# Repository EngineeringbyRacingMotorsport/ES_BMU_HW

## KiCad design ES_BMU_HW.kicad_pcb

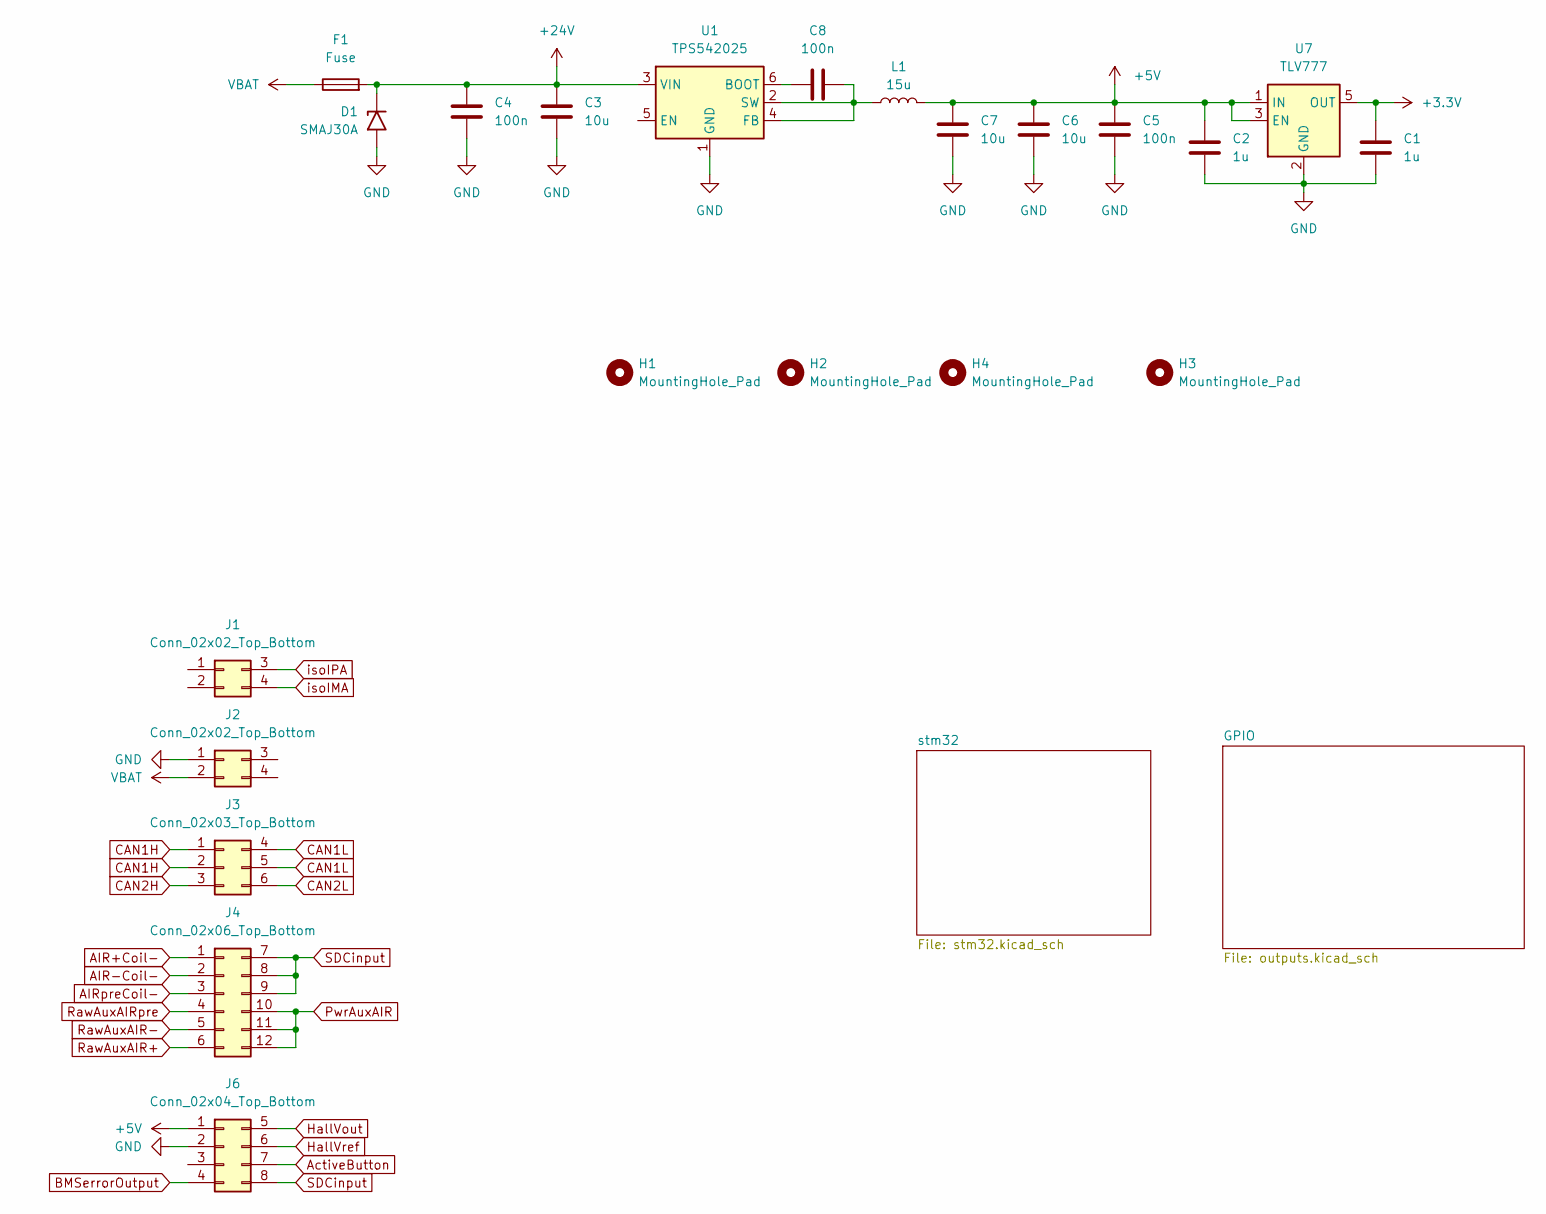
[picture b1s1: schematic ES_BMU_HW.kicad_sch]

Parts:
C1, C2: 1u; C_0603_1608Metric; Part Number VJ0603Y105KXXCW1BC
C3, C6, C7: 10u; C_1206_3216Metric; Part Number VJ1206G106KXATW1BC
C4, C5, C8: 100n; C_0603_1608Metric; Part Number VJ0603Y104KXACW1BC
D1: SMAJ30A; D_SMA; Part Number SMAJ30A
F1: Fuse; Fuse_1206_3216Metric; Part Number JB12S1001R
H1, H2, H3, H4: MountingHole_Pad; MountingHole_3.5mm
J1, J2: Conn_02x02_Top_Bottom; Molex_Nano-Fit_105314-xx04_2x02_P2.50mm_Horizontal
J3: Conn_02x03_Top_Bottom; Molex_Nano-Fit_105314-xx06_2x03_P2.50mm_Horizontal
J4: Conn_02x06_Top_Bottom; Molex_Nano-Fit_105314-xx12_2x06_P2.50mm_Horizontal
J6: Conn_02x04_Top_Bottom; Molex_Nano-Fit_105314-xx08_2x04_P2.50mm_Horizontal
L1: 15u; L_Vishay_IHLP-2020; Part Number IHLP2020CZER150M01
U1: TPS542025; SOT-23-6
U7: TLV777; SOT-23-5; Part Number TLV77712PDBVR

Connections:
+3.3V: C1.1, U7.5 (OUT); also elsewhere on the board
+5V: C2.1, C5.1, C6.1, C7.1, J6.1, L1.2, U7.1 (IN), U7.3 (EN); also elsewhere on the board
+24V: C3.1, C4.1, D1.1 (A1), F1.2, U1.3 (VIN); also elsewhere on the board
AIR+Coil-: J4.1; also elsewhere on the board
AIR-Coil-: J4.2; also elsewhere on the board
AIRpreCoil-: J4.3; also elsewhere on the board
ActiveButton: J6.7; also elsewhere on the board
BMSerrorOutput: J6.4; also elsewhere on the board
CAN1H: J3.1, J3.2; also elsewhere on the board
CAN1L: J3.4, J3.5; also elsewhere on the board
CAN2H: J3.3; also elsewhere on the board
CAN2L: J3.6; also elsewhere on the board
GND: C1.2, C2.2, C3.2, C4.2, C5.2, C6.2, C7.2, D1.2 (A2), J2.1, J6.2, U1.1 (GND), U7.2 (GND), U7.4 (GND); also elsewhere on the board
HallVout: J6.5; also elsewhere on the board
HallVref: J6.6; also elsewhere on the board
unnamed: C8.1, U1.6 (BOOT)
unnamed: C8.2, L1.1, U1.2 (SW), U1.4 (FB)
PwrAuxAIR: J4.10, J4.11, J4.12; also elsewhere on the board
RawAuxAIR+: J4.6; also elsewhere on the board
RawAuxAIR-: J4.5; also elsewhere on the board
RawAuxAIRpre: J4.4; also elsewhere on the board
SDCinput: J4.7, J4.8, J4.9, J6.8; also elsewhere on the board
VBAT: F1.1, J2.2; also elsewhere on the board
isoIMA: J1.4; also elsewhere on the board
isoIPA: J1.3; also elsewhere on the board

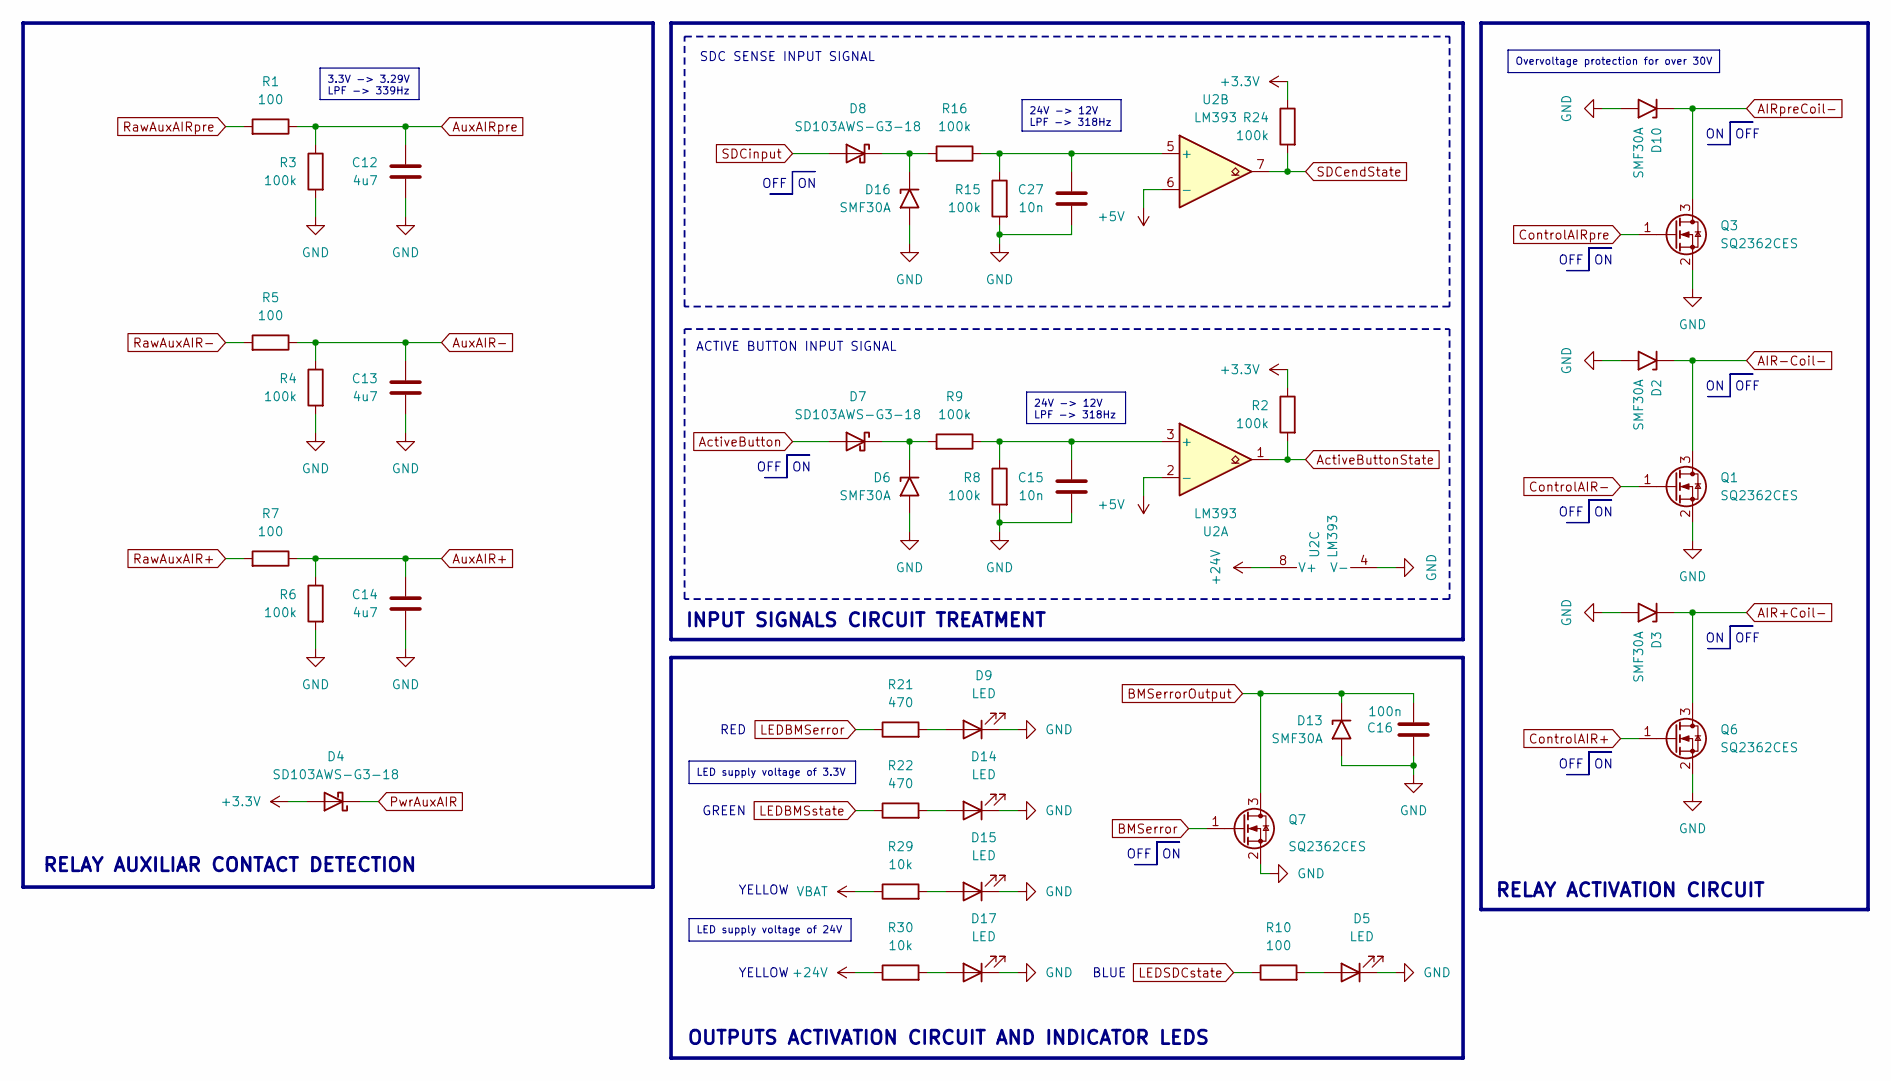
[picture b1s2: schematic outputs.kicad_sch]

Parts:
C12, C13, C14: 4u7; C_0603_1608Metric; Part Number VJ0603G475KXJCW1BC
C15, C27: 10n; C_0603_1608Metric; Part Number VJ0603Y103KXXCW1BC
C16: 100n; C_0603_1608Metric; Part Number VJ0603Y104KXACW1BC
D2, D3, D6, D10, D13, D16: SMF30A; D_SMF; Part Number SMF30A
D4, D7, D8: SD103AWS-G3-18; D_SOD-323_HandSoldering; Part Number SD103AWS-G3-18
D5: LED; LED_0603_1608Metric; Part Number VLMB1300-GS08
D9: LED; LED_0603_1608Metric; Part Number VLMS1300-GS08
D14: LED; LED_0603_1608Metric; Part Number VLMG1300-GS08
D15, D17: LED; LED_0603_1608Metric; Part Number VLMY1300-GS08
Q1, Q3, Q6, Q7: SQ2362CES; SOT-23; Part Number SQ2362CES-T1_GE3
R1, R5, R7: 100; R_0603_1608Metric; Part Number TNPW0603100RBEEA
R2, R3, R4, R6, R8, R9, R15, R16, R24: 100k; R_0603_1608Metric; Part Number TNPW0603100KBEEA
R10: 100; R_0603_1608Metric; Part Number TNPW0603470RBEEA
R21, R22: 470; R_0603_1608Metric; Part Number TNPW0603470RBEEA
R29, R30: 10k; R_0603_1608Metric; Part Number CRCW060310K0FKTAHP
U2: LM393; TSSOP-8_4.4x3mm_P0.65mm; Part Number LM393APWR

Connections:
+3.3V: D4.2 (A), R2.1, R24.1; also elsewhere on the board
+5V: U2.2 (-), U2.6 (-); also elsewhere on the board
+24V: R30.1, U2.8 (V+); also elsewhere on the board
AIR+Coil-: D3.1 (A1), Q6.3 (D); also elsewhere on the board
AIR-Coil-: D2.1 (A1), Q1.3 (D); also elsewhere on the board
AIRpreCoil-: D10.1 (A1), Q3.3 (D); also elsewhere on the board
ActiveButton: D7.2 (A); also elsewhere on the board
ActiveButtonState: R2.2, U2.1; also elsewhere on the board
AuxAIR+: C14.1, R6.1, R7.1; also elsewhere on the board
AuxAIR-: C13.1, R4.1, R5.1; also elsewhere on the board
AuxAIRpre: C12.1, R1.1, R3.1; also elsewhere on the board
BMSerror: Q7.1 (G); also elsewhere on the board
BMSerrorOutput: C16.2, D13.1 (A1), Q7.3 (D); also elsewhere on the board
ControlAIR+: Q6.1 (G); also elsewhere on the board
ControlAIR-: Q1.1 (G); also elsewhere on the board
ControlAIRpre: Q3.1 (G); also elsewhere on the board
GND: C12.2, C13.2, C14.2, C15.2, C16.1, C27.2, D2.2 (A2), D3.2 (A2), D5.1 (K), D6.2 (A2), D9.1 (K), D10.2 (A2), D13.2 (A2), D14.1 (K), D15.1 (K), D16.2 (A2), D17.1 (K), Q1.2 (S), Q3.2 (S), Q6.2 (S), Q7.2 (S), R3.2, R4.2, R6.2, R8.2, R15.2, U2.4 (V-); also elsewhere on the board
LEDBMSerror: R21.1; also elsewhere on the board
LEDBMSstate: R22.1; also elsewhere on the board
LEDSDCstate: R10.1; also elsewhere on the board
unnamed: D5.2 (A), R10.2
unnamed: D6.1 (A1), D7.1 (K), R9.2
unnamed: D9.2 (A), R21.2
unnamed: D14.2 (A), R22.2
unnamed: D15.2 (A), R29.2
unnamed: D8.1 (K), D16.1 (A1), R16.2
unnamed: D17.2 (A), R30.2
unnamed: C15.1, R8.1, R9.1, U2.3 (+)
unnamed: C27.1, R15.1, R16.1, U2.5 (+)
PwrAuxAIR: D4.1 (K); also elsewhere on the board
RawAuxAIR+: R7.2; also elsewhere on the board
RawAuxAIR-: R5.2; also elsewhere on the board
RawAuxAIRpre: R1.2; also elsewhere on the board
SDCendState: R24.2, U2.7; also elsewhere on the board
SDCinput: D8.2 (A); also elsewhere on the board
VBAT: R29.1; also elsewhere on the board

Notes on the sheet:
OFF
ACTIVE BUTTON INPUT SIGNAL
OFF
RED
BLUE
YELLOW
RELAY AUXILIAR CONTACT DETECTION
INPUT SIGNALS CIRCUIT TREATMENT
RELAY ACTIVATION CIRCUIT
SDC SENSE INPUT SIGNAL
OUTPUTS ACTIVATION CIRCUIT AND INDICATOR LEDS
GREEN
24V -> 12V LPF -> 318Hz
3.3V -> 3.29V LPF -> 339Hz
LED supply voltage of 3.3V
LED supply voltage of 24V
Overvoltage protection for over 30V

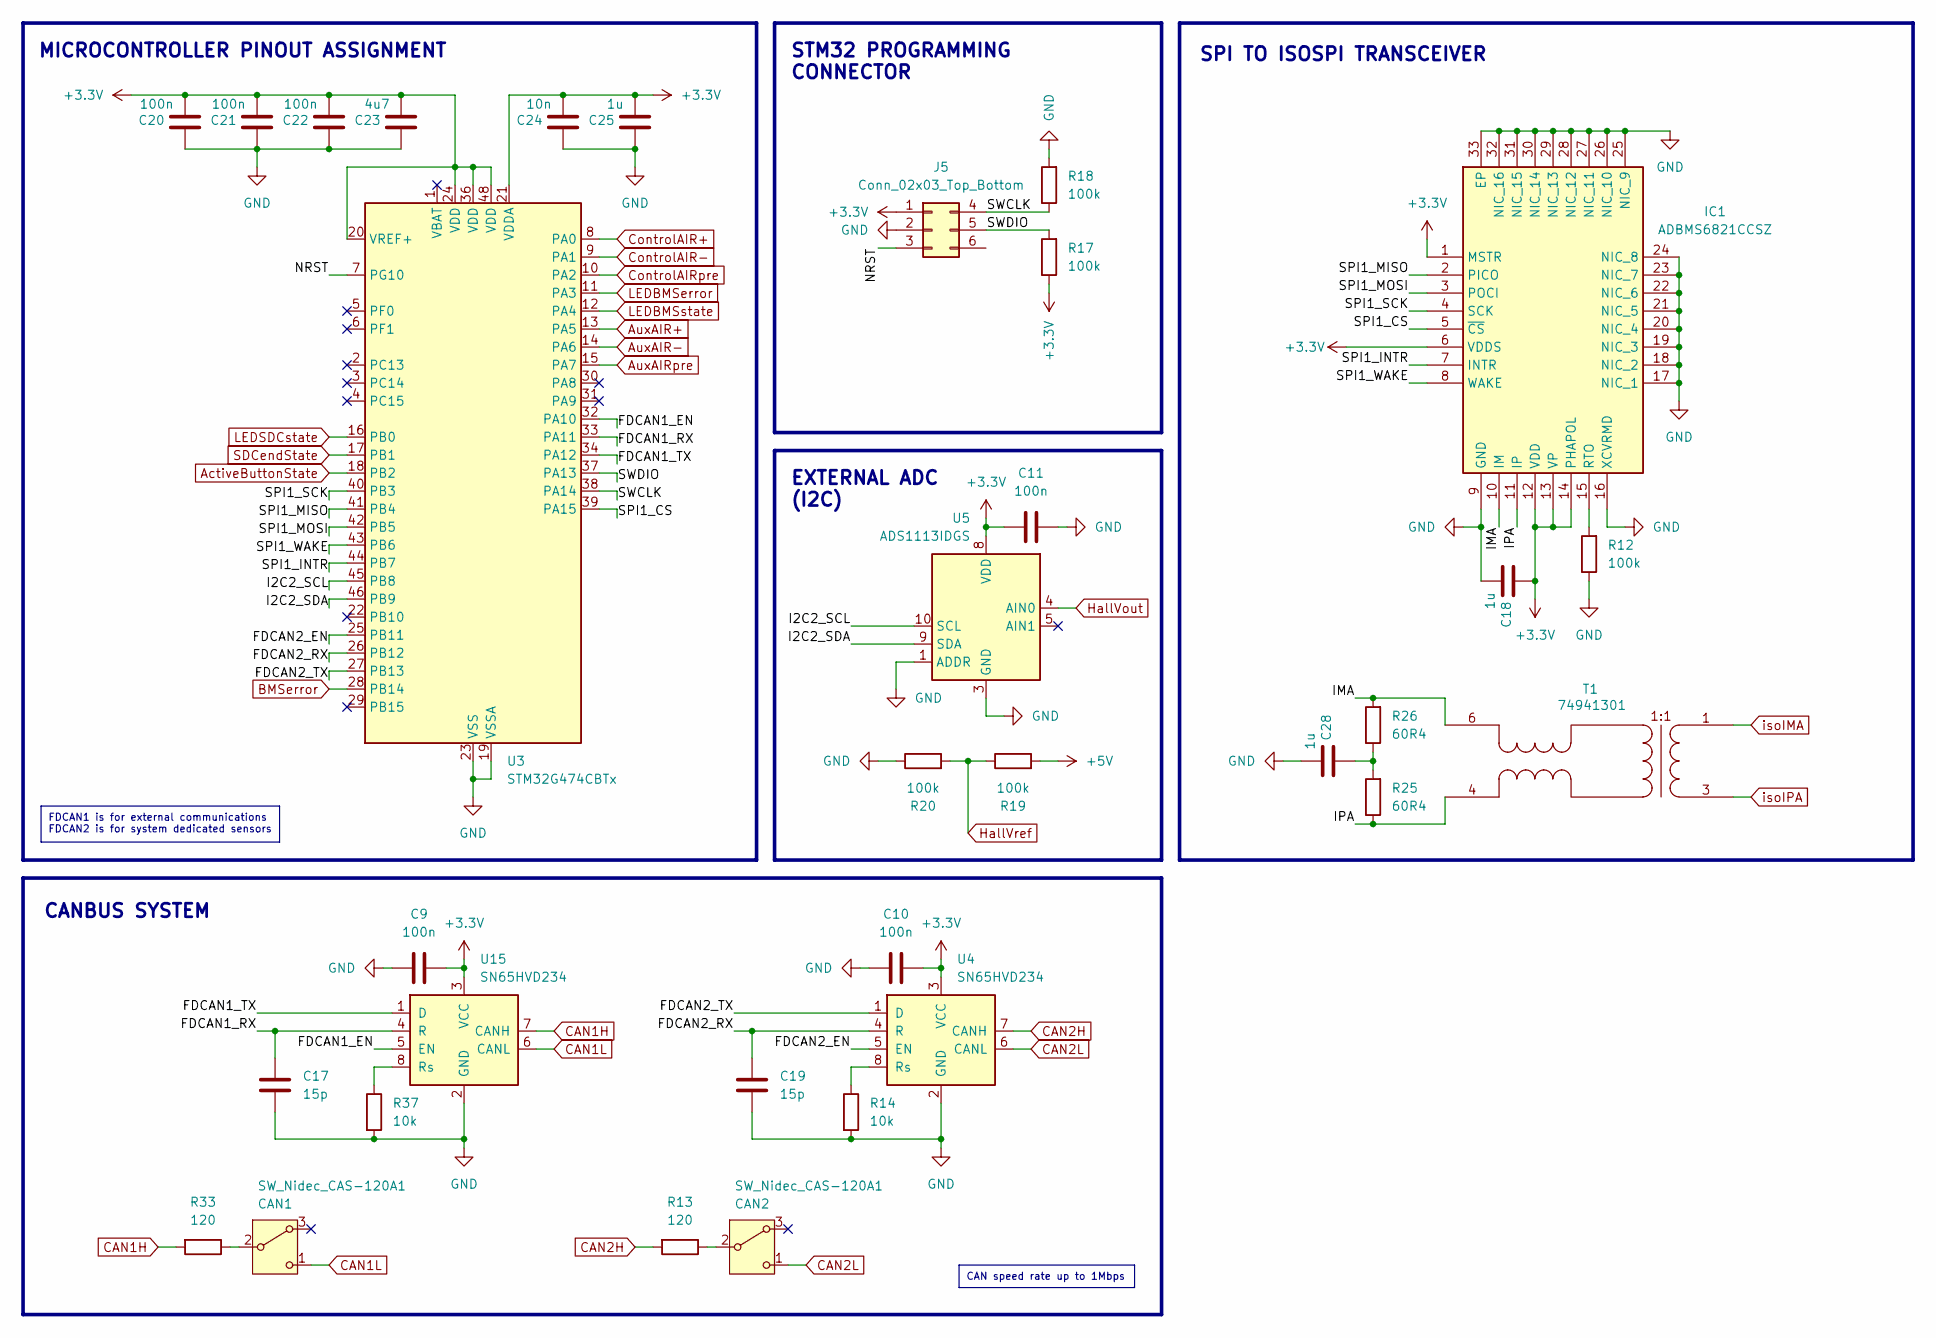
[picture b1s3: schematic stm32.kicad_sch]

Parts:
C9, C10, C11, C20, C21, C22: 100n; C_0603_1608Metric; Part Number VJ0603Y104KXACW1BC
C17, C19: 15p; C_0603_1608Metric; Part Number VJ0603A150JXXCW1BC
C18, C25, C28: 1u; C_0603_1608Metric; Part Number VJ0603Y105KXXCW1BC
C23: 4u7; C_0603_1608Metric; Part Number VJ0603G475KXJCW1BC
C24: 10n; C_0603_1608Metric; Part Number VJ0603Y103KXXCW1BC
CAN1, CAN2: SW_Nidec_CAS-120A1; Nidec_Copal_CAS-120A
IC1: ADBMS6821CCSZ; LFCSP-32-1EP_5x5mm_P0.5mm_EP3.1x3.1mm; Manufacturer_Part_Number ADBMS6821CCSZ; Mouser Part Number 584-ADBMS6821CCSZ
J5: Conn_02x03_Top_Bottom; PinHeader_2x03_P1.27mm_Vertical_SMD; Part Number 61000621121
R12, R17, R18, R19, R20: 100k; R_0603_1608Metric; Part Number TNPW0603100KBEEA
R13, R33: 120; R_0603_1608Metric; Part Number TNPW0603120RBEEA
R14, R37: 10k; R_0603_1608Metric; Part Number CRCW060310K0FKTAHP
R25, R26: 60R4; R_0603_1608Metric; Part Number TNPW060360R4BEEA
T1: 74941301; T_Wurth_WE-BMS_74941301; Working Voltage (V (DC)) 1000; Part Number 74941301
U3: STM32G474CBTx; LQFP-48_7x7mm_P0.5mm; Part Number STM32G474CBT3
U4, U15: SN65HVD234; SOIC-8_3.9x4.9mm_P1.27mm; Part Number SN65HVD234D
U5: ADS1113IDGS; TSSOP-10_3x3mm_P0.5mm; Part Number ADS1113IDGS

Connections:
+3.3V: C9.1, C10.1, C11.1, C18.1, C20.2, C21.2, C22.2, C23.2, C24.2, C25.2, IC1.1 (MSTR), IC1.6 (VDDS), IC1.12 (VDD), IC1.13 (VP), IC1.14 (PHAPOL), J5.1, R17.1, U3.20 (VREF+), U3.21 (VDDA), U3.24 (VDD), U3.36 (VDD), U3.48 (VDD), U4.3 (VCC), U5.8 (VDD), U15.3 (VCC); also elsewhere on the board
+5V: R19.2; also elsewhere on the board
/stm32/FDCAN1_EN: U3.32 (PA10), U15.5 (EN)
/stm32/FDCAN1_RX: C17.1, U3.33 (PA11), U15.4 (R)
/stm32/FDCAN1_TX: U3.34 (PA12), U15.1 (D)
/stm32/FDCAN2_EN: U3.25 (PB11), U4.5 (EN)
/stm32/FDCAN2_RX: C19.1, U3.26 (PB12), U4.4 (R)
/stm32/FDCAN2_TX: U3.27 (PB13), U4.1 (D)
/stm32/I2C2_SCL: U3.45 (PB8), U5.10 (SCL)
/stm32/I2C2_SDA: U3.46 (PB9), U5.9 (SDA)
/stm32/IMA: IC1.10 (IM), R26.2, T1.6
/stm32/IPA: IC1.11 (IP), R25.1, T1.4
/stm32/NRST: J5.3, U3.7 (PG10)
/stm32/SPI1_CS: IC1.5 (~CS), U3.39 (PA15)
/stm32/SPI1_INTR: IC1.7 (INTR), U3.44 (PB7)
/stm32/SPI1_MISO: IC1.2 (PICO), U3.41 (PB4)
/stm32/SPI1_MOSI: IC1.3 (POCI), U3.42 (PB5)
/stm32/SPI1_SCK: IC1.4 (SCK), U3.40 (PB3)
/stm32/SPI1_WAKE: IC1.8 (WAKE), U3.43 (PB6)
/stm32/SWCLK: J5.4, R18.1, U3.38 (PA14)
/stm32/SWDIO: J5.5, R17.2, U3.37 (PA13)
ActiveButtonState: U3.18 (PB2); also elsewhere on the board
AuxAIR+: U3.13 (PA5); also elsewhere on the board
AuxAIR-: U3.14 (PA6); also elsewhere on the board
AuxAIRpre: U3.15 (PA7); also elsewhere on the board
BMSerror: U3.28 (PB14); also elsewhere on the board
CAN1H: R33.2, U15.7 (CANH); also elsewhere on the board
CAN1L: CAN1.1 (C), U15.6 (CANL); also elsewhere on the board
CAN2H: R13.2, U4.7 (CANH); also elsewhere on the board
CAN2L: CAN2.1 (C), U4.6 (CANL); also elsewhere on the board
ControlAIR+: U3.8 (PA0); also elsewhere on the board
ControlAIR-: U3.9 (PA1); also elsewhere on the board
ControlAIRpre: U3.10 (PA2); also elsewhere on the board
GND: C9.2, C10.2, C11.2, C17.2, C18.2, C19.2, C20.1, C21.1, C22.1, C23.1, C24.1, C25.1, C28.2, IC1.9 (GND), IC1.16 (XCVRMD), IC1.17 (NIC_1), IC1.18 (NIC_2), IC1.19 (NIC_3), IC1.20 (NIC_4), IC1.21 (NIC_5), IC1.22 (NIC_6), IC1.23 (NIC_7), IC1.24 (NIC_8), IC1.25 (NIC_9), IC1.26 (NIC_10), IC1.27 (NIC_11), IC1.28 (NIC_12), IC1.29 (NIC_13), IC1.30 (NIC_14), IC1.31 (NIC_15), IC1.32 (NIC_16), IC1.33 (EP), J5.2, R12.1, R14.2, R18.2, R20.1, R37.2, U3.19 (VSSA), U3.23 (VSS), U3.35 (VSS), U3.47 (VSS), U4.2 (GND), U5.1 (ADDR), U5.3 (GND), U15.2 (GND); also elsewhere on the board
HallVout: U5.4 (AIN0); also elsewhere on the board
HallVref: R19.1, R20.2; also elsewhere on the board
LEDBMSerror: U3.11 (PA3); also elsewhere on the board
LEDBMSstate: U3.12 (PA4); also elsewhere on the board
LEDSDCstate: U3.16 (PB0); also elsewhere on the board
unnamed: C28.1, R25.2, R26.1
unnamed: CAN1.2 (B), R33.1
unnamed: CAN2.2 (B), R13.1
unnamed: IC1.15 (RTO), R12.2
unnamed: R14.1, U4.8 (Rs)
unnamed: R37.1, U15.8 (Rs)
SDCendState: U3.17 (PB1); also elsewhere on the board
isoIMA: T1.1; also elsewhere on the board
isoIPA: T1.3; also elsewhere on the board

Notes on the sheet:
STM32 PROGRAMMING CONNECTOR
SPI TO ISOSPI TRANSCEIVER
EXTERNAL ADC (I2C)
CANBUS SYSTEM
MICROCONTROLLER PINOUT ASSIGNMENT
FDCAN1 is for external communications FDCAN2 is for system dedicated sensors
CAN speed rate up to 1Mbps

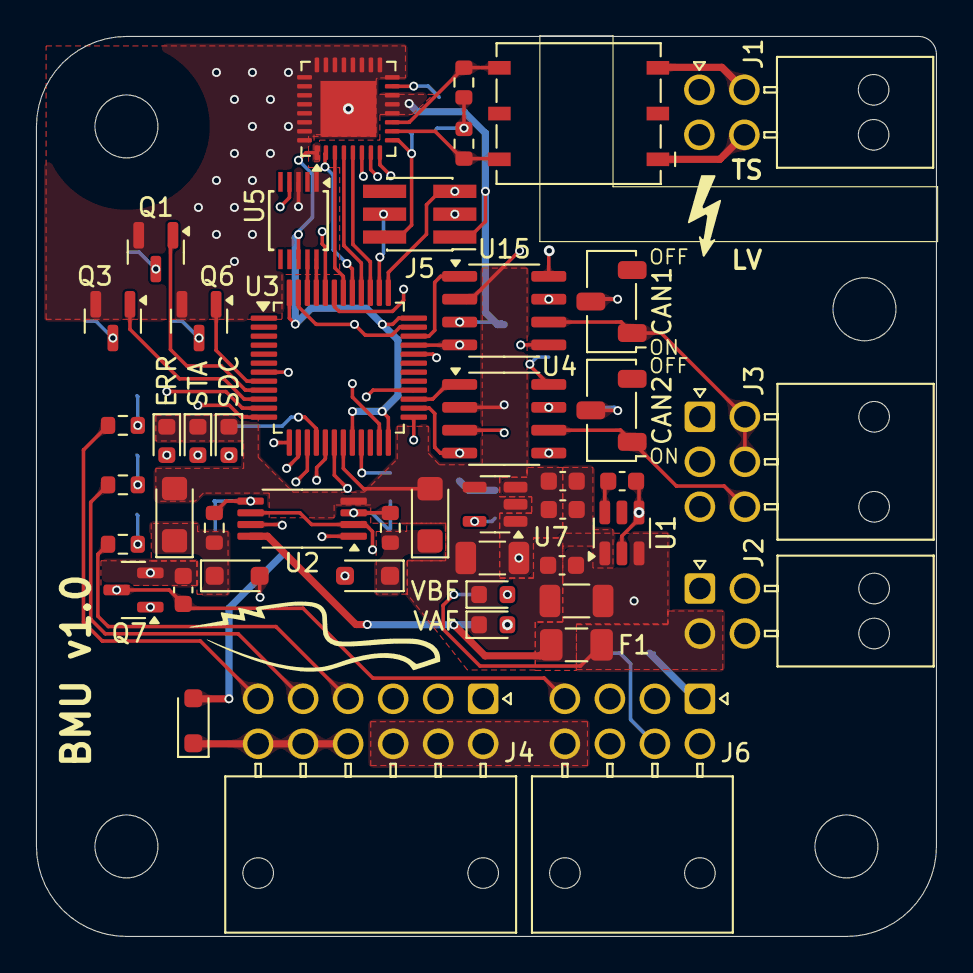
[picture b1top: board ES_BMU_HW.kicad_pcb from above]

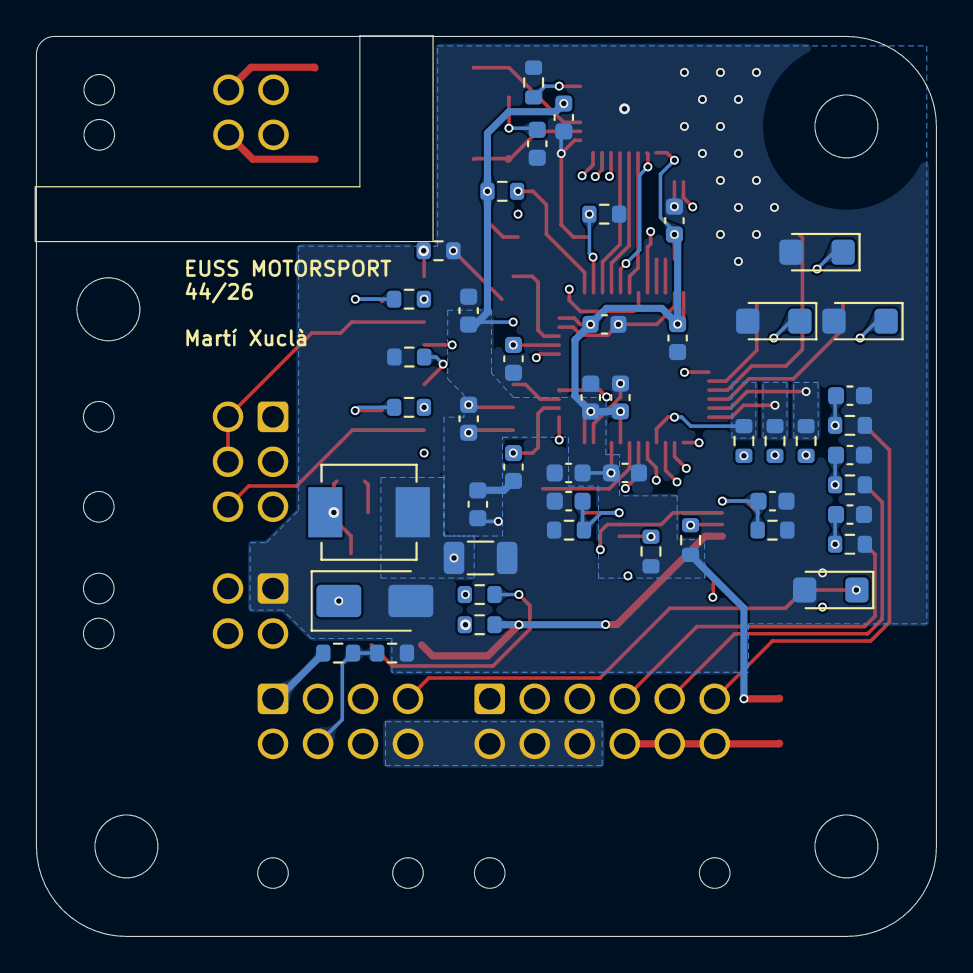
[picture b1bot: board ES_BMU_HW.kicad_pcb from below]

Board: 4 copper layers, 50.0 x 50.0 mm, 97 parts (47 on the bottom side), 71 nets.
